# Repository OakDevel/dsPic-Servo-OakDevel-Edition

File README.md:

# dsPic-Servo-OakDevel-Edition
Servo Motor Control with dsPic based on YAPSC.

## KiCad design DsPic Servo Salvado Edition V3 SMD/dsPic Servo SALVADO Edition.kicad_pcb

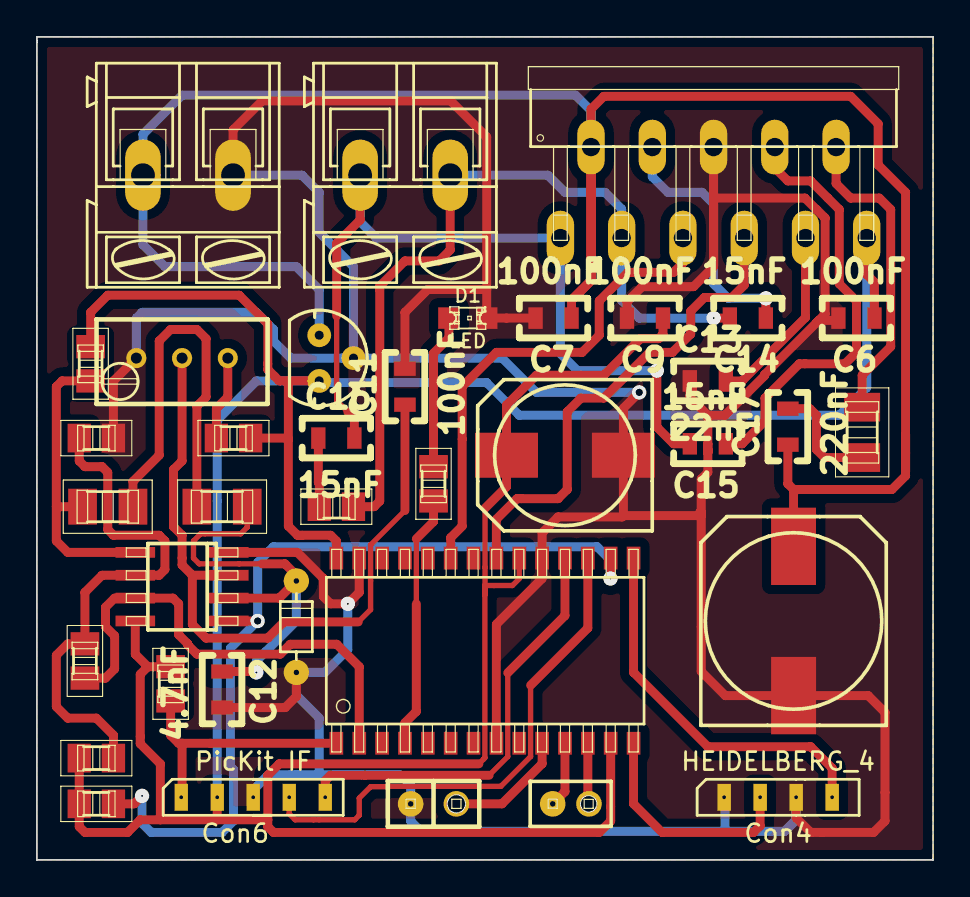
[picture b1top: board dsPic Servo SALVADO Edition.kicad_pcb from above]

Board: 2 copper layers, 49.8 x 45.7 mm, 37 parts (0 on the bottom side), 31 nets.

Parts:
C6, C7, C9, C11: 100nF; CAP-SMD-0805
C8: 100uF; 140CLH-1010
C10: 10uF; 140CLH-0810
C12: 4.7nF; CAP-SMD-0805
C13: 22nF; CAP-SMD-0805
C14, C15, C16: 15nF; CAP-SMD-0805
C17: 220nF; CAP-SMD-0805
Con3: 24 V; CON-PTR500-AK300_2
Con4: HEIDELBERG_4; HDLBRG4
Con5: RC15; pinhead-1X02
Con6: PicKit IF; HDLBRG5
Con7: MOTOR; CON-PTR500-AK300_2
D1: LED; LED-0805
D2: 1N4148; DIODE-D-5
IC2: dsPIC30F4012; SO-28W
IC3: LM2904; SO-08
IC4: L6203; ZIP-11
J1: Prog; pinhead-1X02M
R5: 470; M0805
R6: 10K; M0805
R7: 33K; M0805
R8: 10K; POT-TRIM-T93YA
R9, R11: 1K; M1206
R10: 3K; M0805
R12, R13, R14: 1K; M0805
R15: 4K7; M0805
R16: 7R5; M0805
RSense1: .47R; M1206
Reg1: 7805; v-reg-78LXX

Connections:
+5V: C6.1, C9.1, C10.1, Con6.2, IC2.13, IC2.20, IC2.28, IC3.8, IC4.11, R6.1, R7.1, R10.1, R12.2, R13.1, Reg1.3
+24V: C7.1, C8.1, C17.1, Con3.2, IC4.2, Reg1.1
/CPU/AN0: IC2.2, IC3.7, R15.1
/CPU/RC15: Con5.1, IC2.10
GND: C6.2, C7.2, C8.2, C9.2, C10.2, C11.2, C12.2, C13.1, Con3.1, Con4.1, Con4.3, Con5.2, Con6.3, D1.2, D2.A, IC2.8, IC2.19, IC2.27, IC3.4, IC4.6, R8.3, R14.2, Reg1.2
I_SENSE: R9.1, R11.2
LSENSE: IC4.10, RSense1.2
MCLR: Con6.1, IC2.1, R6.2
unnamed: C11.1, IC3.3, R8.2
unnamed: C12.1, D2.K, IC3.2, R9.2
unnamed: C13.2, IC4.9
unnamed: C14.1, IC4.4
unnamed: C14.2, Con7.1, IC4.3, R16.2
unnamed: C15.1, IC4.8
unnamed: C15.2, C16.2, Con7.2, IC4.1
unnamed: C16.1, R16.1
unnamed: C17.2, RSense1.1
unnamed: Con4.2, IC2.14
unnamed: Con4.4, IC2.15
unnamed: D1.1, R5.2
unnamed: IC2.4, R5.1
unnamed: IC2.11, J1.2
unnamed: IC2.12, J1.1
unnamed: IC2.16, IC3.1, R10.2
unnamed: IC3.5, R11.1, R13.2
unnamed: IC3.6, R12.1, R14.1, R15.2
unnamed: R7.2, R8.1
PGC: Con6.5, IC2.18
PGD: Con6.4, IC2.17
PWM_H_A: IC2.23, IC4.5
PWM_H_B: IC2.21, IC4.7

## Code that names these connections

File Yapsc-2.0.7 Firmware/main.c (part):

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// pll16 needs a 30mhz part
//_FOSC( FRC_PLL16 );  // 6mhz * PLL16  / 4 = 24mips
//_FWDT(WDT_OFF);                   // wdt off
/* enablebrownout @4.2v, 64ms powerup delay, MCLR pin active */
/* pwm pins in use, both active low to give 64ms delay on powerup */
//_FBORPOR(PBOR_ON & BORV_42 & PWRT_64 & MCLR_EN & RST_PWMPIN & PWMxL_ACT_LO );
//_FBORPOR(MCLR_EN & PBOR_ON & BORV_42 & RST_PWMPIN & PWMxH_ACT_HI & PWMxL_ACT_HI);
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	_TRISE8 = 1;			// Current limit input pin : FLTA

	// PORT F				// 0=output, 1=input
	_TRISF2 = 1;			// PGC used by icsp
	_TRISF3 = 1;			// PGD used by icsp
}

/*********************************************************************
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
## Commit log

2017-09-04 Deleted Directory
